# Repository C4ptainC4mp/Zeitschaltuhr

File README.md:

# Zeitschaltuhr. 
time switch, supporting 8 AC outputs (10A max) and a 5V DC PWM output (2A max). 

This is a time switch supporting 8 AC outputs and a 5V DC PWM output. It also offers visualization with a LC-Display, configuration by a 2 button interface, a Real-Time-Clock(RTC) powered by a SuperCap and an on-board AC/DC power module.  

The combined switched power of all the AC outputs should not exceed 16A while a single output is limited to 10A. The DC PWM output is limited to 2A by the 15W IRM-15-5 AC/DC power module, more power output might be possible by selecting a better power module and power mosfet.

The current output status is presented by a 4x40 Character LC-Display. The first line shows the current time while the lines 2 to 4 show the outputs. Only 3 outputs are shown at once, it is possible to scroll trough the other outputs by pressing the scroll button.

In case of an blackout, the RTC is powered by a supercap for at least a week.  

It is possible to reconfigure the names and times by scrolling the target output to line 2 and pressing the select button.

The USB-B port is used to power the device while programming and debuging.

MCU: Microchip PIC18F26k22<br />
RTC: Microchip MCP 7940N (7940M also, but without backup power)<br />
LCD: ERM4004SBS-1 (2x KS0066 (HD44780 compatible))<br />

/demo includes a photo of the front and back side of the finished time switch.

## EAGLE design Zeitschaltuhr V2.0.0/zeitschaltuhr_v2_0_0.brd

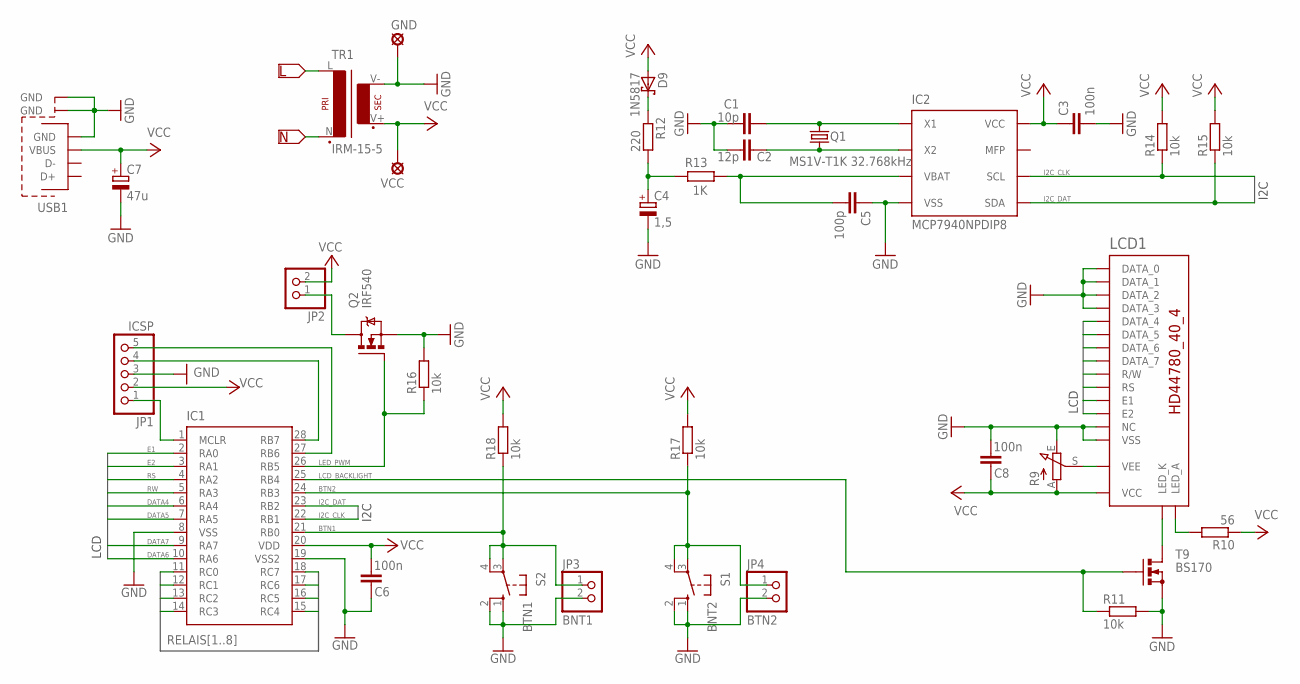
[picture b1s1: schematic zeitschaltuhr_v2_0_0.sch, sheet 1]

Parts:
C1: 10p; C025-024X044
C2: 12p; C025-024X044
C3, C6, C8: 100n; C025-024X044
C4: 1,5; DDL155S05F2CRRDAPZHORIZONTAL
C5: 100p; C025-024X044
C7: 47u; E2-5
D9: 1N5817; DO41-7
GND: LSP13
IC1: PIC18F26K22DIP28; DIP28
IC2: MCP7940NPDIP8; DIL8
JP1: ICSP; 1X05
JP2: PINHD-1X2; 1X02
JP3: BNT1; 1X02
JP4: BTN2; 1X02
LCD1: HD44780_4_40; HD44780_40_4
Q1: MS1V-T1K 32.768kHz; MS1V-T1K_SMD
Q2: IRF540; TO220BV
R9: 3306P-1-103
R10: 56; 0207/10
R11, R14, R15, R16, R17, R18: 10k; 0207/10
R12: 220; 0207/10
R13: 1K; 0207/10
S1: BNT2; B3F-10XX
S2: BTN1; B3F-10XX
T9: BS170; TO92-
TR1: IRM-15-5; IRM-15
USB1: USB_TYPE_B_THT; USB_TYPE_B_USB-B-S-RA
VCC: LSP13

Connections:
BTN1: IC1.21 (RB0), JP3.1, R18.1, S2.3, S2.4 (P1)
BTN2: IC1.24 (RB3), JP4.1, R17.1, S1.3, S1.4 (P1)
DATA4: IC1.6 (RA4), LCD1.4 (DATA_4)
DATA5: IC1.7 (RA5), LCD1.3 (DATA_5)
DATA6: IC1.10 (RA6), LCD1.2 (DATA_6)
DATA7: IC1.9 (RA7), LCD1.1 (DATA_7)
E1: IC1.2 (RA0), LCD1.9 (E1)
E2: IC1.3 (RA1), LCD1.15 (E2)
GND: C1.1, C2.1, C3.2, C4.-, C5.1, C6.1, C7.-, C8.2, GND.MP, IC1.8 (VSS), IC1.19 (VSS2), IC2.4 (VSS), JP1.3, JP3.2, JP4.2, LCD1.5 (DATA_3), LCD1.6 (DATA_2), LCD1.7 (DATA_1), LCD1.8 (DATA_0), LCD1.13 (VSS), LCD1.16 (NC), Q2.S, R9.E, R11.2, R16.2, S1.1 (S), S1.2 (S1), S2.1 (S), S2.2 (S1), T9.S, TR1.V-, USB1.GND@1 (GND), USB1.GND@2 (GND), USB1.GND@3 (GND); also elsewhere on the board
I2C_CLK: IC1.22 (RB1), IC2.6 (SCL), R14.1
I2C_DAT: IC1.23 (RB2), IC2.5 (SDA), R15.1
L: TR1.L; also elsewhere on the board
LCD_BACKLIGHT: IC1.25 (RB4), R11.1, T9.G
LED_A: LCD1.17 (LED_A), R10.2
LED_K: LCD1.18 (LED_K), T9.D
LED_PWM: IC1.26 (RB5), Q2.G, R16.1
N: TR1.N; also elsewhere on the board
unnamed: C1.2, IC2.1 (X1), Q1.1
unnamed: C2.2, IC2.2 (X2), Q1.2
unnamed: C4.+, R12.2, R13.2
unnamed: D9.C, R12.1
unnamed: C5.2, IC2.3 (VBAT), R13.1
unnamed: IC1.1 (MCLR), JP1.1
unnamed: IC1.28 (RB7), JP1.4
unnamed: IC1.27 (RB6), JP1.5
unnamed: JP2.1, Q2.D
RELAIS1: IC1.11 (RC0); also elsewhere on the board
RELAIS2: IC1.12 (RC1); also elsewhere on the board
RELAIS3: IC1.13 (RC2); also elsewhere on the board
RELAIS4: IC1.14 (RC3); also elsewhere on the board
RELAIS5: IC1.15 (RC4); also elsewhere on the board
RELAIS6: IC1.16 (RC5); also elsewhere on the board
RELAIS7: IC1.17 (RC6); also elsewhere on the board
RELAIS8: IC1.18 (RC7); also elsewhere on the board
RS: IC1.4 (RA2), LCD1.11 (RS)
RW: IC1.5 (RA3), LCD1.10 (R/W)
VCC: C3.1, C6.2, C7.+, C8.1, D9.A, IC1.20 (VDD), IC2.8 (VCC), JP1.2, JP2.2, LCD1.14 (VCC), R9.A, R10.1, R14.2, R15.2, R17.2, R18.2, TR1.V+, USB1.VBUS, VCC.MP; also elsewhere on the board
VEE: LCD1.12 (VEE), R9.S

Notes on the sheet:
I2C
LCD

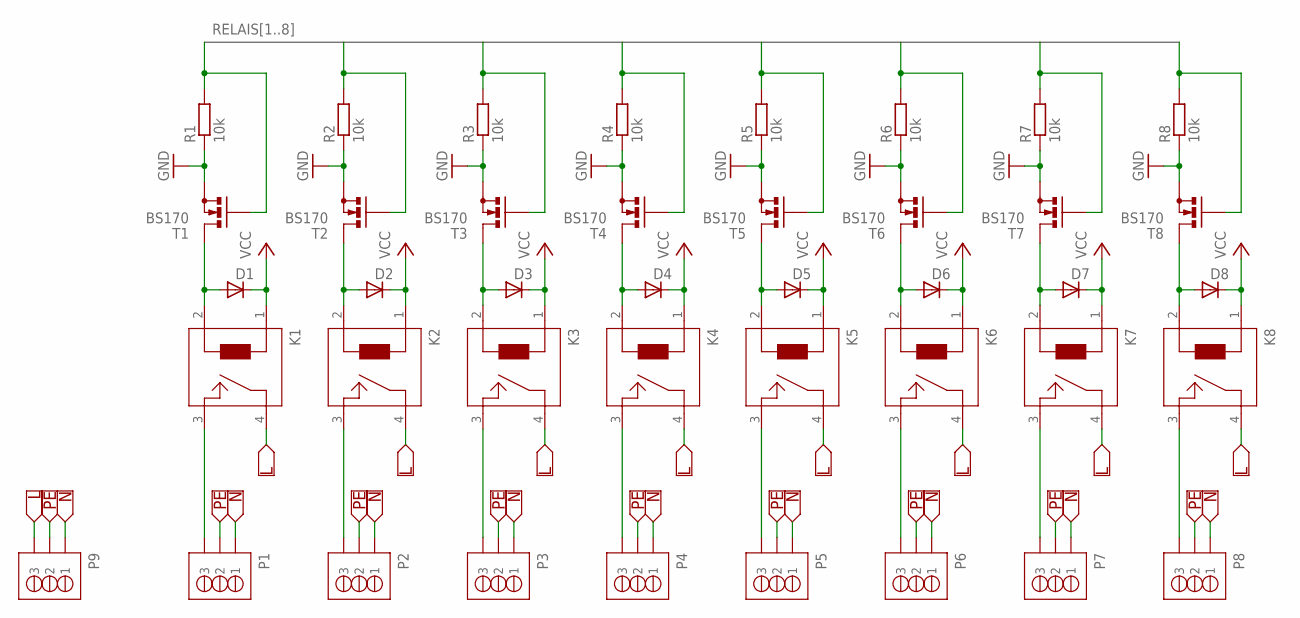
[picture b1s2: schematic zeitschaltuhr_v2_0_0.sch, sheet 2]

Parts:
D1, D2, D3, D4, D5, D6, D7, D8: 1N4148; DO35-7
K1, K2, K3, K4, K5, K6, K7, K8: OJE-SS-105HM,000
P1, P2, P3, P4, P5, P6, P7, P8, P9: TERMINAL_BLOCK_MB310-500M03
R1, R2, R3, R4, R5, R6, R7, R8: 10k; 0207/10
T1, T2, T3, T4, T5, T6, T7, T8: BS170; TO92-

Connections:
GND: R1.1, R2.1, R3.1, R4.1, R5.1, R6.1, R7.1, R8.1, T1.S, T2.S, T3.S, T4.S, T5.S, T6.S, T7.S, T8.S; also elsewhere on the board
L: K1.4, K2.4, K3.4, K4.4, K5.4, K6.4, K7.4, K8.4, P9.3; also elsewhere on the board
N: P1.1, P2.1, P3.1, P4.1, P5.1, P6.1, P7.1, P8.1, P9.1; also elsewhere on the board
unnamed: D1.A, K1.2, T1.D
unnamed: D2.A, K2.2, T2.D
unnamed: D3.A, K3.2, T3.D
unnamed: D4.A, K4.2, T4.D
unnamed: K1.3, P1.3
unnamed: K2.3, P2.3
unnamed: D5.A, K5.2, T5.D
unnamed: D6.A, K6.2, T6.D
unnamed: D7.A, K7.2, T7.D
unnamed: D8.A, K8.2, T8.D
unnamed: K3.3, P3.3
unnamed: K4.3, P4.3
unnamed: K5.3, P5.3
unnamed: K6.3, P6.3
unnamed: K7.3, P7.3
unnamed: K8.3, P8.3
PE: P1.2, P2.2, P3.2, P4.2, P5.2, P6.2, P7.2, P8.2, P9.2
RELAIS1: R1.2, T1.G; also elsewhere on the board
RELAIS2: R2.2, T2.G; also elsewhere on the board
RELAIS3: R3.2, T3.G; also elsewhere on the board
RELAIS4: R4.2, T4.G; also elsewhere on the board
RELAIS5: R5.2, T5.G; also elsewhere on the board
RELAIS6: R6.2, T6.G; also elsewhere on the board
RELAIS7: R7.2, T7.G; also elsewhere on the board
RELAIS8: R8.2, T8.G; also elsewhere on the board
VCC: D1.C, D2.C, D3.C, D4.C, D5.C, D6.C, D7.C, D8.C, K1.1, K2.1, K3.1, K4.1, K5.1, K6.1, K7.1, K8.1; also elsewhere on the board

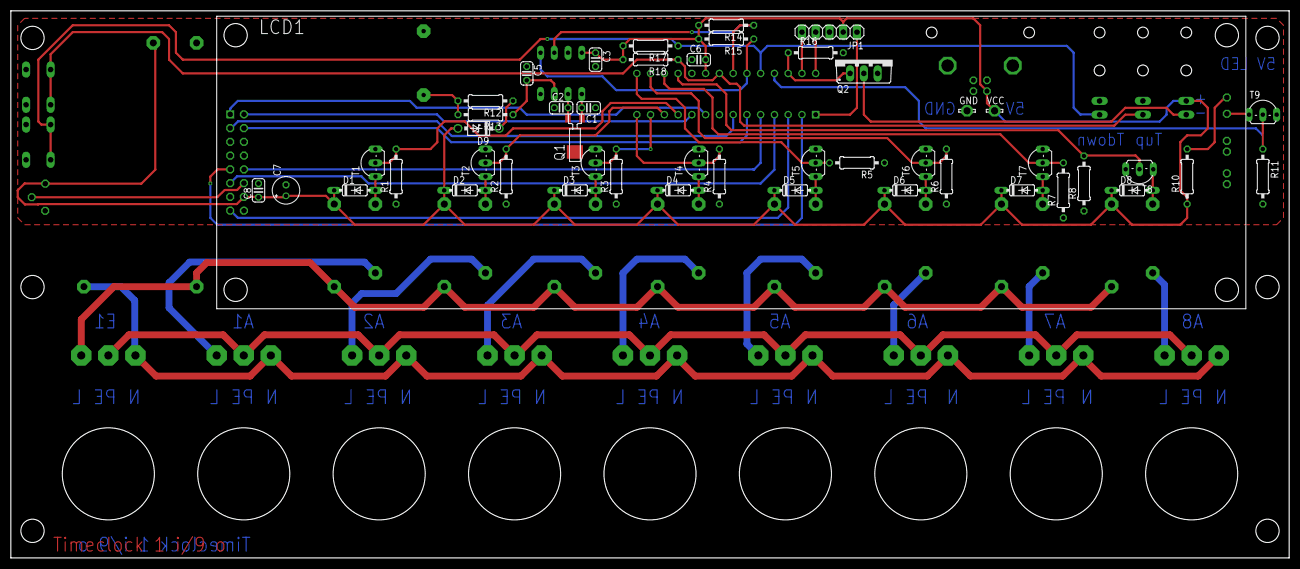
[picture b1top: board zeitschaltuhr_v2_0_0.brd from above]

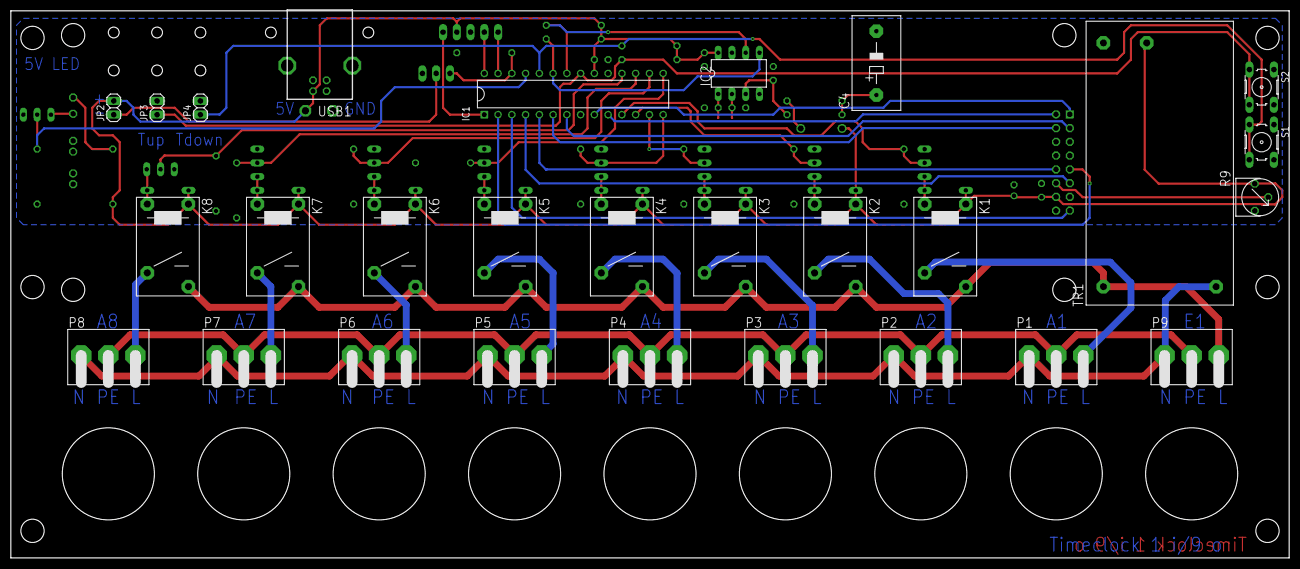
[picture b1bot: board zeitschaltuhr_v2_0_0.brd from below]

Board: 2 copper layers, 236.0 x 101.0 mm, 76 parts (28 on the bottom side), 55 nets.

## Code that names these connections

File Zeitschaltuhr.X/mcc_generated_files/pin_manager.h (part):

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// get/set IO_RA0 aliases
#define IO_RA0_TRIS               TRISAbits.TRISA0
#define IO_RA0_LAT                LATAbits.LATA0
#define IO_RA0_PORT               PORTAbits.RA0
#define IO_RA0_ANS                ANSELAbits.ANSA0
#define IO_RA0_SetHigh()            do { LATAbits.LATA0 = 1; } while(0)
#define IO_RA0_SetLow()             do { LATAbits.LATA0 = 0; } while(0)
#define IO_RA0_Toggle()             do { LATAbits.LATA0 = ~LATAbits.LATA0; } while(0)
#define IO_RA0_GetValue()           PORTAbits.RA0
#define IO_RA0_SetDigitalInput()    do { TRISAbits.TRISA0 = 1; } while(0)
#define IO_RA0_SetDigitalOutput()   do { TRISAbits.TRISA0 = 0; } while(0)
#define IO_RA0_SetAnalogMode()  do { ANSELAbits.ANSA0 = 1; } while(0)
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// get/set IO_RA1 aliases
#define IO_RA1_TRIS               TRISAbits.TRISA1
#define IO_RA1_LAT                LATAbits.LATA1
#define IO_RA1_PORT               PORTAbits.RA1
#define IO_RA1_ANS                ANSELAbits.ANSA1
#define IO_RA1_SetHigh()            do { LATAbits.LATA1 = 1; } while(0)
#define IO_RA1_SetLow()             do { LATAbits.LATA1 = 0; } while(0)
#define IO_RA1_Toggle()             do { LATAbits.LATA1 = ~LATAbits.LATA1; } while(0)
#define IO_RA1_GetValue()           PORTAbits.RA1
#define IO_RA1_SetDigitalInput()    do { TRISAbits.TRISA1 = 1; } while(0)
#define IO_RA1_SetDigitalOutput()   do { TRISAbits.TRISA1 = 0; } while(0)
#define IO_RA1_SetAnalogMode()  do { ANSELAbits.ANSA1 = 1; } while(0)
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// get/set IO_RA2 aliases
#define IO_RA2_TRIS               TRISAbits.TRISA2
#define IO_RA2_LAT                LATAbits.LATA2
#define IO_RA2_PORT               PORTAbits.RA2
#define IO_RA2_ANS                ANSELAbits.ANSA2
#define IO_RA2_SetHigh()            do { LATAbits.LATA2 = 1; } while(0)
#define IO_RA2_SetLow()             do { LATAbits.LATA2 = 0; } while(0)
#define IO_RA2_Toggle()             do { LATAbits.LATA2 = ~LATAbits.LATA2; } while(0)
#define IO_RA2_GetValue()           PORTAbits.RA2
#define IO_RA2_SetDigitalInput()    do { TRISAbits.TRISA2 = 1; } while(0)
#define IO_RA2_SetDigitalOutput()   do { TRISAbits.TRISA2 = 0; } while(0)
#define IO_RA2_SetAnalogMode()  do { ANSELAbits.ANSA2 = 1; } while(0)
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// get/set IO_RA3 aliases
#define IO_RA3_TRIS               TRISAbits.TRISA3
#define IO_RA3_LAT                LATAbits.LATA3
#define IO_RA3_PORT               PORTAbits.RA3
#define IO_RA3_ANS                ANSELAbits.ANSA3
#define IO_RA3_SetHigh()            do { LATAbits.LATA3 = 1; } while(0)
#define IO_RA3_SetLow()             do { LATAbits.LATA3 = 0; } while(0)
#define IO_RA3_Toggle()             do { LATAbits.LATA3 = ~LATAbits.LATA3; } while(0)
#define IO_RA3_GetValue()           PORTAbits.RA3
#define IO_RA3_SetDigitalInput()    do { TRISAbits.TRISA3 = 1; } while(0)
#define IO_RA3_SetDigitalOutput()   do { TRISAbits.TRISA3 = 0; } while(0)
#define IO_RA3_SetAnalogMode()  do { ANSELAbits.ANSA3 = 1; } while(0)
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// get/set IO_RA4 aliases
#define IO_RA4_TRIS               TRISAbits.TRISA4
#define IO_RA4_LAT                LATAbits.LATA4
#define IO_RA4_PORT               PORTAbits.RA4
#define IO_RA4_SetHigh()            do { LATAbits.LATA4 = 1; } while(0)
#define IO_RA4_SetLow()             do { LATAbits.LATA4 = 0; } while(0)
#define IO_RA4_Toggle()             do { LATAbits.LATA4 = ~LATAbits.LATA4; } while(0)
#define IO_RA4_GetValue()           PORTAbits.RA4
#define IO_RA4_SetDigitalInput()    do { TRISAbits.TRISA4 = 1; } while(0)
#define IO_RA4_SetDigitalOutput()   do { TRISAbits.TRISA4 = 0; } while(0)

// get/set IO_RA5 aliases
#define IO_RA5_TRIS               TRISAbits.TRISA5
#define IO_RA5_LAT                LATAbits.LATA5
#define IO_RA5_PORT               PORTAbits.RA5
#define IO_RA5_ANS                ANSELAbits.ANSA5
#define IO_RA5_SetHigh()            do { LATAbits.LATA5 = 1; } while(0)
#define IO_RA5_SetLow()             do { LATAbits.LATA5 = 0; } while(0)
#define IO_RA5_Toggle()             do { LATAbits.LATA5 = ~LATAbits.LATA5; } while(0)
#define IO_RA5_GetValue()           PORTAbits.RA5
#define IO_RA5_SetDigitalInput()    do { TRISAbits.TRISA5 = 1; } while(0)
#define IO_RA5_SetDigitalOutput()   do { TRISAbits.TRISA5 = 0; } while(0)
#define IO_RA5_SetAnalogMode()  do { ANSELAbits.ANSA5 = 1; } while(0)
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// get/set IO_RA6 aliases
#define IO_RA6_TRIS               TRISAbits.TRISA6
#define IO_RA6_LAT                LATAbits.LATA6
#define IO_RA6_PORT               PORTAbits.RA6
#define IO_RA6_SetHigh()            do { LATAbits.LATA6 = 1; } while(0)
#define IO_RA6_SetLow()             do { LATAbits.LATA6 = 0; } while(0)
#define IO_RA6_Toggle()             do { LATAbits.LATA6 = ~LATAbits.LATA6; } while(0)
#define IO_RA6_GetValue()           PORTAbits.RA6
#define IO_RA6_SetDigitalInput()    do { TRISAbits.TRISA6 = 1; } while(0)
#define IO_RA6_SetDigitalOutput()   do { TRISAbits.TRISA6 = 0; } while(0)

// get/set IO_RA7 aliases
#define IO_RA7_TRIS               TRISAbits.TRISA7
#define IO_RA7_LAT                LATAbits.LATA7
#define IO_RA7_PORT               PORTAbits.RA7
#define IO_RA7_SetHigh()            do { LATAbits.LATA7 = 1; } while(0)
#define IO_RA7_SetLow()             do { LATAbits.LATA7 = 0; } while(0)
#define IO_RA7_Toggle()             do { LATAbits.LATA7 = ~LATAbits.LATA7; } while(0)
#define IO_RA7_GetValue()           PORTAbits.RA7
#define IO_RA7_SetDigitalInput()    do { TRISAbits.TRISA7 = 1; } while(0)
#define IO_RA7_SetDigitalOutput()   do { TRISAbits.TRISA7 = 0; } while(0)

// get/set IO_RB0 aliases
#define IO_RB0_TRIS               TRISBbits.TRISB0
#define IO_RB0_LAT                LATBbits.LATB0
#define IO_RB0_PORT               PORTBbits.RB0
#define IO_RB0_WPU                WPUBbits.WPUB0
#define IO_RB0_ANS                ANSELBbits.ANSB0
#define IO_RB0_SetHigh()            do { LATBbits.LATB0 = 1; } while(0)
#define IO_RB0_SetLow()             do { LATBbits.LATB0 = 0; } while(0)
#define IO_RB0_Toggle()             do { LATBbits.LATB0 = ~LATBbits.LATB0; } while(0)
#define IO_RB0_GetValue()           PORTBbits.RB0
#define IO_RB0_SetDigitalInput()    do { TRISBbits.TRISB0 = 1; } while(0)
#define IO_RB0_SetDigitalOutput()   do { TRISBbits.TRISB0 = 0; } while(0)
#define IO_RB0_SetPullup()      do { WPUBbits.WPUB0 = 1; } while(0)
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#define RB1_SetHigh()    do { LATBbits.LATB1 = 1; } while(0)
#define RB1_SetLow()   do { LATBbits.LATB1 = 0; } while(0)
#define RB1_Toggle()   do { LATBbits.LATB1 = ~LATBbits.LATB1; } while(0)
#define RB1_GetValue()         PORTBbits.RB1
#define RB1_SetDigitalInput()   do { TRISBbits.TRISB1 = 1; } while(0)
#define RB1_SetDigitalOutput()  do { TRISBbits.TRISB1 = 0; } while(0)
#define RB1_SetPullup()     do { WPUBbits.WPUB1 = 1; } while(0)
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#define RB2_SetHigh()    do { LATBbits.LATB2 = 1; } while(0)
#define RB2_SetLow()   do { LATBbits.LATB2 = 0; } while(0)
#define RB2_Toggle()   do { LATBbits.LATB2 = ~LATBbits.LATB2; } while(0)
#define RB2_GetValue()         PORTBbits.RB2
#define RB2_SetDigitalInput()   do { TRISBbits.TRISB2 = 1; } while(0)
#define RB2_SetDigitalOutput()  do { TRISBbits.TRISB2 = 0; } while(0)
#define RB2_SetPullup()     do { WPUBbits.WPUB2 = 1; } while(0)
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// get/set IO_RB3 aliases
#define IO_RB3_TRIS               TRISBbits.TRISB3
#define IO_RB3_LAT                LATBbits.LATB3
#define IO_RB3_PORT               PORTBbits.RB3
#define IO_RB3_WPU                WPUBbits.WPUB3
#define IO_RB3_ANS                ANSELBbits.ANSB3
#define IO_RB3_SetHigh()            do { LATBbits.LATB3 = 1; } while(0)
#define IO_RB3_SetLow()             do { LATBbits.LATB3 = 0; } while(0)
#define IO_RB3_Toggle()             do { LATBbits.LATB3 = ~LATBbits.LATB3; } while(0)
#define IO_RB3_GetValue()           PORTBbits.RB3
#define IO_RB3_SetDigitalInput()    do { TRISBbits.TRISB3 = 1; } while(0)
#define IO_RB3_SetDigitalOutput()   do { TRISBbits.TRISB3 = 0; } while(0)
#define IO_RB3_SetPullup()      do { WPUBbits.WPUB3 = 1; } while(0)
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#define RB4_SetHigh()    do { LATBbits.LATB4 = 1; } while(0)
#define RB4_SetLow()   do { LATBbits.LATB4 = 0; } while(0)
#define RB4_Toggle()   do { LATBbits.LATB4 = ~LATBbits.LATB4; } while(0)
#define RB4_GetValue()         PORTBbits.RB4
#define RB4_SetDigitalInput()   do { TRISBbits.TRISB4 = 1; } while(0)
#define RB4_SetDigitalOutput()  do { TRISBbits.TRISB4 = 0; } while(0)
#define RB4_SetPullup()     do { WPUBbits.WPUB4 = 1; } while(0)
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#define RB5_SetHigh()    do { LATBbits.LATB5 = 1; } while(0)
#define RB5_SetLow()   do { LATBbits.LATB5 = 0; } while(0)
#define RB5_Toggle()   do { LATBbits.LATB5 = ~LATBbits.LATB5; } while(0)
#define RB5_GetValue()         PORTBbits.RB5
#define RB5_SetDigitalInput()   do { TRISBbits.TRISB5 = 1; } while(0)
#define RB5_SetDigitalOutput()  do { TRISBbits.TRISB5 = 0; } while(0)
#define RB5_SetPullup()     do { WPUBbits.WPUB5 = 1; } while(0)
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// get/set IO_RB6 aliases
#define IO_RB6_TRIS               TRISBbits.TRISB6
#define IO_RB6_LAT                LATBbits.LATB6
#define IO_RB6_PORT               PORTBbits.RB6
#define IO_RB6_WPU                WPUBbits.WPUB6
#define IO_RB6_SetHigh()            do { LATBbits.LATB6 = 1; } while(0)
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
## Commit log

2019-02-17 initial commit
    schematic and PCB layout
2019-02-17 Added demo pictures
2019-02-23 Create LICENSE

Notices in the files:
Zeitschaltuhr.X/mcc_generated_files/pin_manager.h:
Copyright (c) 2013 - 2015 released Microchip Technology Inc.  All rights reserved.
